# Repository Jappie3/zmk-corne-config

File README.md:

# Crkbd ZMK config

## Packages

This flake contains the following packages:

- `crosstool-ng` -> cross-toolchain generator used by Zephyr
    - Takes about 20 minutes to build*
- `zephyr-sdk` -> RTOS for multiple hardware architectures
    - Takes about 1h15m to build*
- `corne_left`, `corne_right`, `zmk_reset`:
    - ZMK firmware for the left & right halves of my wireless Corne, built with the config in `config/`
    - `zmk_reset` -> `settings_reset` shield, see https://zmk.dev/docs/troubleshooting#split-keyboard-halves-unable-to-pair for more info

Note: these packages are configured for the `arm-cortex_a15-linux-gnueabihf` architecture and the `arm-zephyr-eabi` toolchain, as specified by two variables at the top of the flake.

\* Build times are measured on a laptop with an AMD Ryzen 7 5800H (16 cores @ 4.46GHz)

## Repo structure

```
.
├── config
├── corne-ultralight-pcb
└── zmk-zephyr
```

`config/` contains my personal ZMK config files.

All the Kicad files in `corne-ultralight-pcb` were originally copied from [petejohanson's fork of foostan's crkbd repo](https://github.com/petejohanson/crkbd/tree/board/corne-ultralight/corne-ultralight/pcb), more specifically the `corne-ultralight` branch. This branch added support for the `nice!view` display, I then modded the PCB to support Cherry Hotswap sockets.

The `zmk-zephyr/` directory contains the minimal files necessary to run `west manifest --resolve`. The bash script in that directory can be used to parse the repos & revisions from `west manifest --resolve` to the `builtins.fetchTarball` format that Nix can use.

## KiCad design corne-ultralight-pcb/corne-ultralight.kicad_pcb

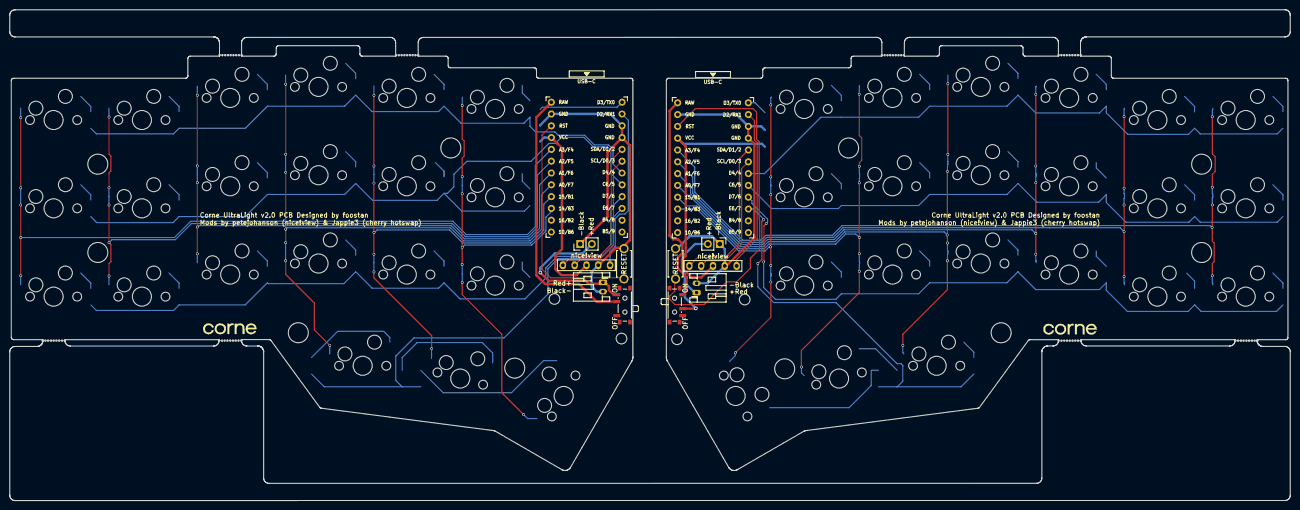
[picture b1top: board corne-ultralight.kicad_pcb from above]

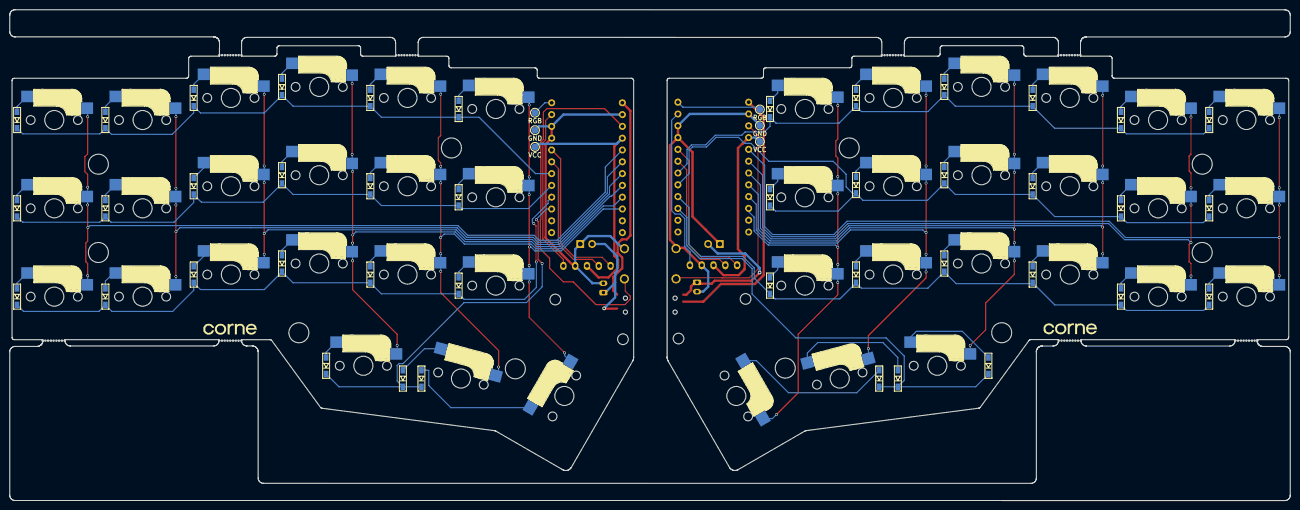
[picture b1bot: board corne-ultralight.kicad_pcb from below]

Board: 2 copper layers, 275.5 x 105.6 mm, 124 parts (60 on the bottom side), 80 nets.

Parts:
BATJ1, BATJ3: Conn_01x02_Female; PinHeader_1x02_P2.54mm_Vertical
BATJ2, BATJ4: Conn_01x02_Female; JST_PH_S2B-PH-K_1x02_P2.00mm_Horizontal
D1, D2, D3, D4, D5, D6, D7, D8, D9, D10, D11, D12, D13, D14, D15, D16, D17, D18, D19, D20, D21, D22, D23, D24, D25, D26, D27, D28, D29, D30, D31, D32, D33, D34, D35, D36, D37, D38, D39, D40, D41, D42: D; D3_SMD_v2
J2, J7: OLED; nice_view_1side
J5, J5#2, J5#3, J5#4, J5#5, J5#6, J5#7, J5#8: Breakaway_Tabs
PSW1, PSW2: SW_SPST; SW_SPDT_PCM12
RSW1, RSW1#2: SW_PUSH; ResetSW_1side
Ref**: Val**; thread_m2
Ref**#2, Ref**#8, Ref**#9: Val**; thread_m2
Ref**#3, Ref**#4, Ref**#5, Ref**#6, Ref**#7, Ref**#10, Ref**#11, Ref**#12, Ref**#13, Ref**#14: Val**; spacer_m2
SW1, SW2, SW3, SW4, SW5, SW6, SW7, SW8, SW9, SW10, SW11, SW12, SW13, SW14, SW15, SW16, SW17, SW18, SW19, SW20, SW21, SW22, SW23, SW24, SW25, SW26, SW27, SW28, SW29, SW30, SW31, SW32, SW33, SW34, SW35, SW36, SW37, SW38, SW39, SW40, SW41, SW42: SW_PUSH; CherryMX_Hotswap
TP1, TP4: RGB; TestPoint_Pad_D1.5mm
TP2, TP5: VCC; TestPoint_Pad_D1.5mm
TP3, TP6: GND; TestPoint_Pad_D1.5mm
U1, U2: ProMicro; ProMicro_v3

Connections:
+BATT: PSW1.2 (B), U1.24 (RAW)
+BATTA: PSW2.1 (A), U2.24 (RAW)
CS: J2.5, U1.2 (RX1/D2)
CS_r: J7.5, U2.2 (RX1/D2)
GND: BATJ1.1, BATJ2.2, J2.4, RSW1#2.2, TP3.1, U1.3 (GND), U1.4 (GND), U1.23 (GND)
GNDA: BATJ3.1, BATJ4.2, J7.4, RSW1.2, TP6.1, U2.3 (GND), U2.4 (GND), U2.23 (GND)
unnamed: BATJ1.2, BATJ2.1, PSW1.3 (C)
unnamed: BATJ3.2, BATJ4.1, PSW2.2 (B)
unnamed: D1.2 (A), SW1.2
unnamed: D2.2 (A), SW2.2
unnamed: D3.2 (A), SW3.2
unnamed: D4.2 (A), SW4.2
unnamed: D5.2 (A), SW5.2
unnamed: D6.2 (A), SW6.2
unnamed: D7.2 (A), SW7.2
unnamed: D8.2 (A), SW8.2
unnamed: D9.2 (A), SW9.2
unnamed: D10.2 (A), SW10.2
unnamed: D11.2 (A), SW11.2
unnamed: D12.2 (A), SW12.2
unnamed: D13.2 (A), SW13.2
unnamed: D14.2 (A), SW14.2
unnamed: D15.2 (A), SW15.2
unnamed: D16.2 (A), SW16.2
unnamed: D17.2 (A), SW17.2
unnamed: D18.2 (A), SW18.2
unnamed: D19.2 (A), SW19.2
unnamed: D20.2 (A), SW20.2
unnamed: D21.2 (A), SW21.2
unnamed: D22.2 (A), SW22.2
unnamed: D23.2 (A), SW23.2
unnamed: D24.2 (A), SW24.2
unnamed: D25.2 (A), SW25.2
unnamed: D26.2 (A), SW26.2
unnamed: D27.2 (A), SW27.2
unnamed: D28.2 (A), SW28.2
unnamed: D29.2 (A), SW29.2
unnamed: D30.2 (A), SW30.2
unnamed: D31.2 (A), SW31.2
unnamed: D32.2 (A), SW32.2
unnamed: D33.2 (A), SW33.2
unnamed: D34.2 (A), SW34.2
unnamed: D35.2 (A), SW35.2
unnamed: D36.2 (A), SW36.2
unnamed: D37.2 (A), SW37.2
unnamed: D38.2 (A), SW38.2
unnamed: D39.2 (A), SW39.2
unnamed: D40.2 (A), SW40.2
unnamed: D41.2 (A), SW41.2
unnamed: D42.2 (A), SW42.2
RGB: TP1.1, U1.1 (TX0/D3)
RGB_r: TP4.1, U2.1 (TX0/D3)
SCL: J2.2, U1.6 (3/D0/SCL)
SCL_r: J7.2, U2.6 (3/D0/SCL)
SDA: J2.1, U1.5 (2/D1/SDA)
SDA_r: J7.1, U2.5 (2/D1/SDA)
VCC: J2.3, TP2.1, U1.21 (VCC)
VDD: J7.3, TP5.1, U2.21 (VCC)
col0: SW1.1, SW7.1, SW13.1, U1.20 (F4/A3)
col0_r: SW22.1, SW28.1, SW34.1, U2.20 (F4/A3)
col1: SW2.1, SW8.1, SW14.1, U1.19 (F5/A2)
col1_r: SW23.1, SW29.1, SW35.1, U2.19 (F5/A2)
col2: SW3.1, SW9.1, SW15.1, U1.18 (F6/A1)
col2_r: SW24.1, SW30.1, SW36.1, U2.18 (F6/A1)
col3: SW4.1, SW10.1, SW16.1, SW19.1, U1.17 (F7/A0)
col3_r: SW25.1, SW31.1, SW37.1, SW40.1, U2.17 (F7/A0)
col4: SW5.1, SW11.1, SW17.1, SW20.1, U1.16 (B1/15)
col4_r: SW26.1, SW32.1, SW38.1, SW41.1, U2.16 (B1/15)
col5: SW6.1, SW12.1, SW18.1, SW21.1, U1.15 (B3/14)
col5_r: SW27.1, SW33.1, SW39.1, SW42.1, U2.15 (B3/14)
reset: RSW1#2.1, U1.22 (RST)
reset_r: RSW1.1, U2.22 (RST)
row0: D1.1 (K), D2.1 (K), D3.1 (K), D4.1 (K), D5.1 (K), D6.1 (K), U1.7 (4/D4)
row0_r: D22.1 (K), D23.1 (K), D24.1 (K), D25.1 (K), D26.1 (K), D27.1 (K), U2.7 (4/D4)
row1: D7.1 (K), D8.1 (K), D9.1 (K), D10.1 (K), D11.1 (K), D12.1 (K), U1.8 (5/C6)
row1_r: D28.1 (K), D29.1 (K), D30.1 (K), D31.1 (K), D32.1 (K), D33.1 (K), U2.8 (5/C6)
row2: D13.1 (K), D14.1 (K), D15.1 (K), D16.1 (K), D17.1 (K), D18.1 (K), U1.9 (6/D7)
row2_r: D34.1 (K), D35.1 (K), D36.1 (K), D37.1 (K), D38.1 (K), D39.1 (K), U2.9 (6/D7)
row3: D19.1 (K), D20.1 (K), D21.1 (K), U1.10 (7/E6)
row3_r: D40.1 (K), D41.1 (K), D42.1 (K), U2.10 (7/E6)

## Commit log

2024-04-19 flake: init
2024-04-19 flake: fix shield name
2024-04-19 feat: add Corne config files
2024-04-19 feat: add zmk west manifests
2024-04-20 flake: add board variable to zmkFirmware
2024-04-20 flake: add zmk_reset package
2024-04-20 flake: add tio to devshell
2024-04-20 flake: rename zmk_left & zmk_right to corne_left & corne_right
2024-04-20 flake: remove some comments
2024-04-20 refactor: rename zmk directory to zmk-zephyr
2024-04-20 style: cleanup code & comments
2024-04-20 docs: add readme
2024-04-24 flake: change cmsis module name
2024-05-02 feat: disable wpm
2024-05-02 feat: enable USB logging
2024-05-02 feat: display config
2024-05-02 fix: set correct cs pin for nice!view
2024-05-02 fix: specify correct pin for nice!view CS
2024-05-02 feat: add pcb files
2024-05-02 docs: PCB files
